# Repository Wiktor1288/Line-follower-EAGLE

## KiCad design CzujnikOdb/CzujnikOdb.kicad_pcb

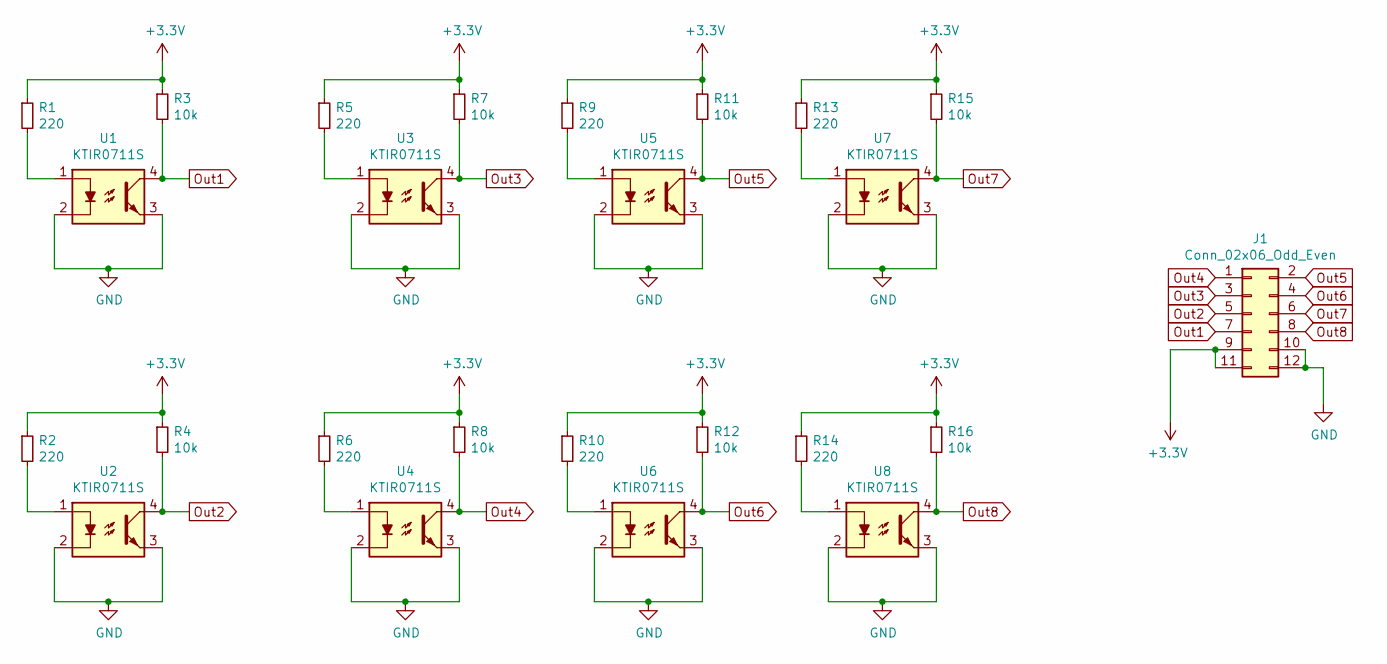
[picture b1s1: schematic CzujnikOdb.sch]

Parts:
J1: Conn_02x06_Odd_Even; PinHeader_2x06_P2.54mm_Vertical
R1, R2, R5, R6, R9, R10, R13, R14: 220; R_0805_2012Metric_Pad1.20x1.40mm_HandSolder
R3, R4, R7, R8, R11, R12, R15, R16: 10k; R_0805_2012Metric_Pad1.20x1.40mm_HandSolder
U1, U2, U3, U4, U5, U6, U7, U8: KTIR0711S

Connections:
+3V3: J1.9, J1.11, R1.1, R2.1, R3.1, R4.1, R5.1, R6.1, R7.1, R8.1, R9.1, R10.1, R11.1, R12.1, R13.1, R14.1, R15.1, R16.1
GND: J1.10, J1.12, U1.2, U1.3, U2.2, U2.3, U3.2, U3.3, U4.2, U4.3, U5.2, U5.3, U6.2, U6.3, U7.2, U7.3, U8.2, U8.3
unnamed: R1.2, U1.1
unnamed: R2.2, U2.1
unnamed: R5.2, U3.1
unnamed: R6.2, U4.1
unnamed: R9.2, U5.1
unnamed: R10.2, U6.1
unnamed: R13.2, U7.1
unnamed: R14.2, U8.1
Out1: J1.7, R3.2, U1.4
Out2: J1.5, R4.2, U2.4
Out3: J1.3, R7.2, U3.4
Out4: J1.1, R8.2, U4.4
Out5: J1.2, R11.2, U5.4
Out6: J1.4, R12.2, U6.4
Out7: J1.6, R15.2, U7.4
Out8: J1.8, R16.2, U8.4

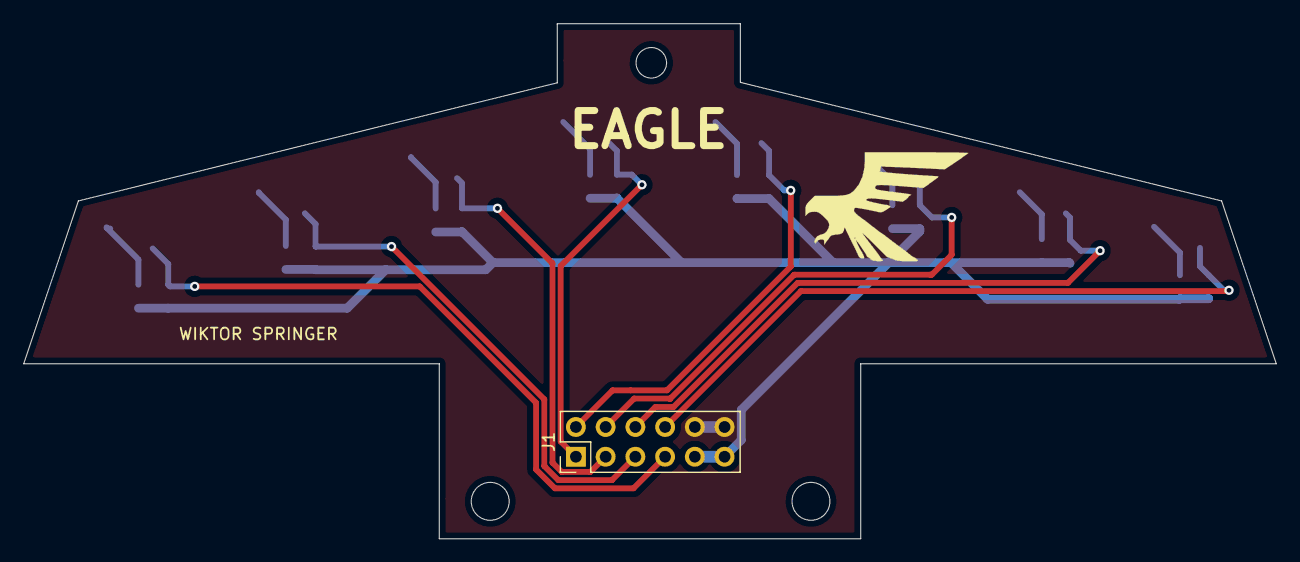
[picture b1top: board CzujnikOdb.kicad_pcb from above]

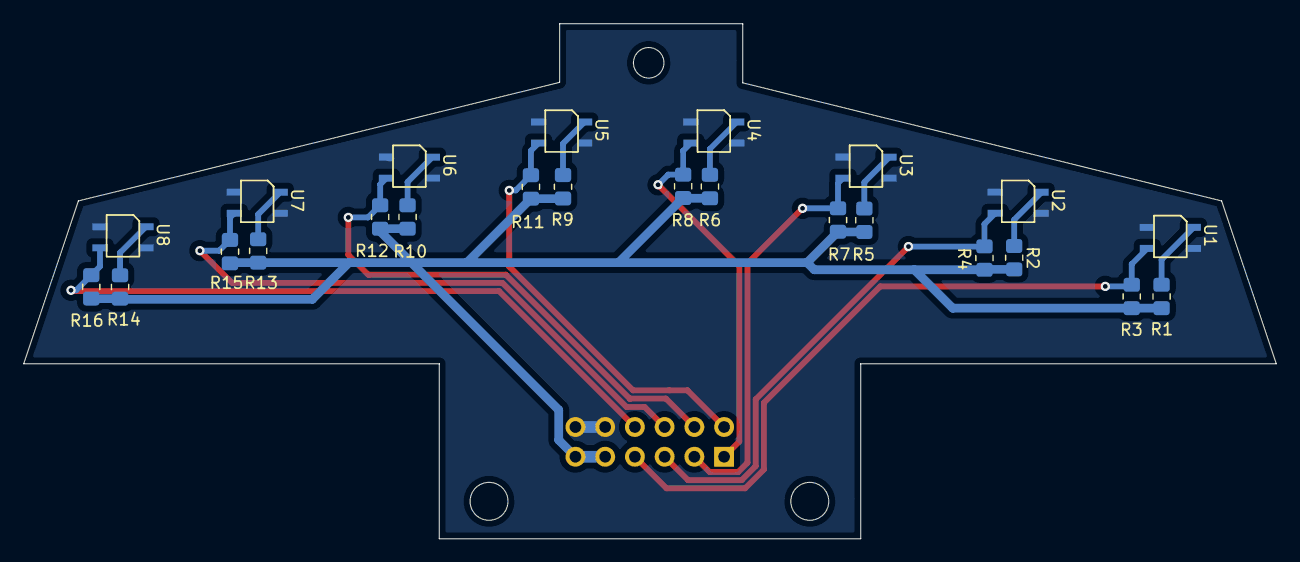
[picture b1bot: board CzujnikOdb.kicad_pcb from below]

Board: 2 copper layers, 107.0 x 44.0 mm, 25 parts (24 on the bottom side), 18 nets.

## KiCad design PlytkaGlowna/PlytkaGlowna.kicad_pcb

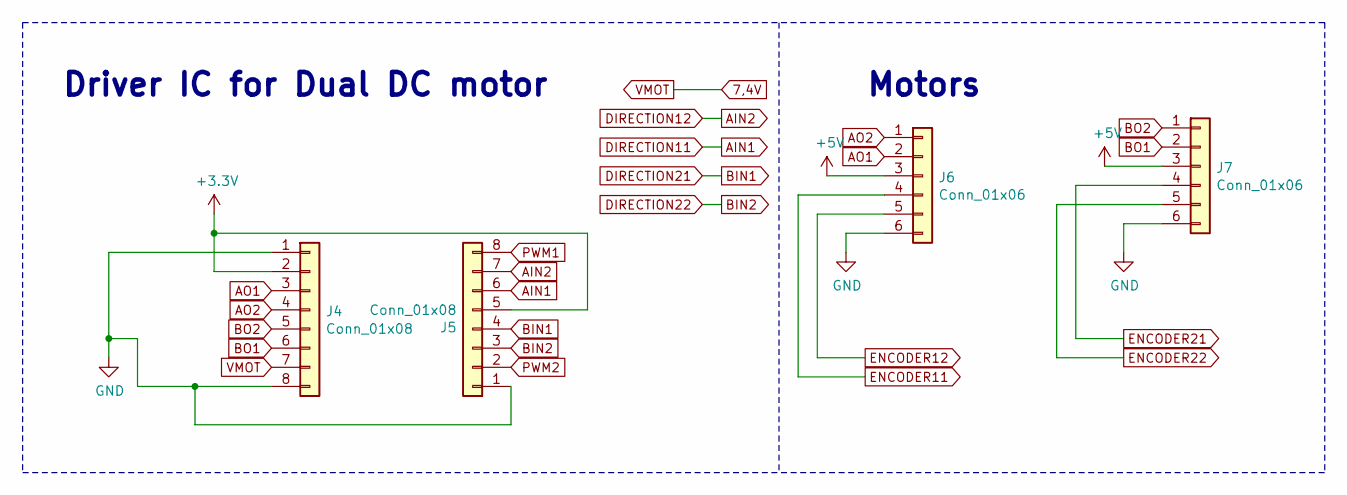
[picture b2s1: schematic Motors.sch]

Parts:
J4, J5: Conn_01x08; PinSocket_1x08_P2.54mm_Vertical
J6, J7: Conn_01x06; PinSocket_1x06_P2.54mm_Vertical

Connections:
7,4V: J4.7; also elsewhere on the board
+5V: J6.3, J7.3; also elsewhere on the board
AIN1: J5.6; also elsewhere on the board
AIN2: J5.7; also elsewhere on the board
AO1: J4.3, J6.2
AO2: J4.4, J6.1
BIN1: J5.4; also elsewhere on the board
BIN2: J5.3; also elsewhere on the board
BO1: J4.6, J7.2
BO2: J4.5, J7.1
ENCODER11: J6.4; also elsewhere on the board
ENCODER12: J6.5; also elsewhere on the board
ENCODER21: J7.4; also elsewhere on the board
ENCODER22: J7.5; also elsewhere on the board
GND: J4.1, J4.8, J5.1, J6.6, J7.6; also elsewhere on the board
PWM1: J5.8; also elsewhere on the board
PWM2: J5.2; also elsewhere on the board
VDD: J4.2, J5.5; also elsewhere on the board

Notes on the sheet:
Driver IC for Dual DC motor
Motors

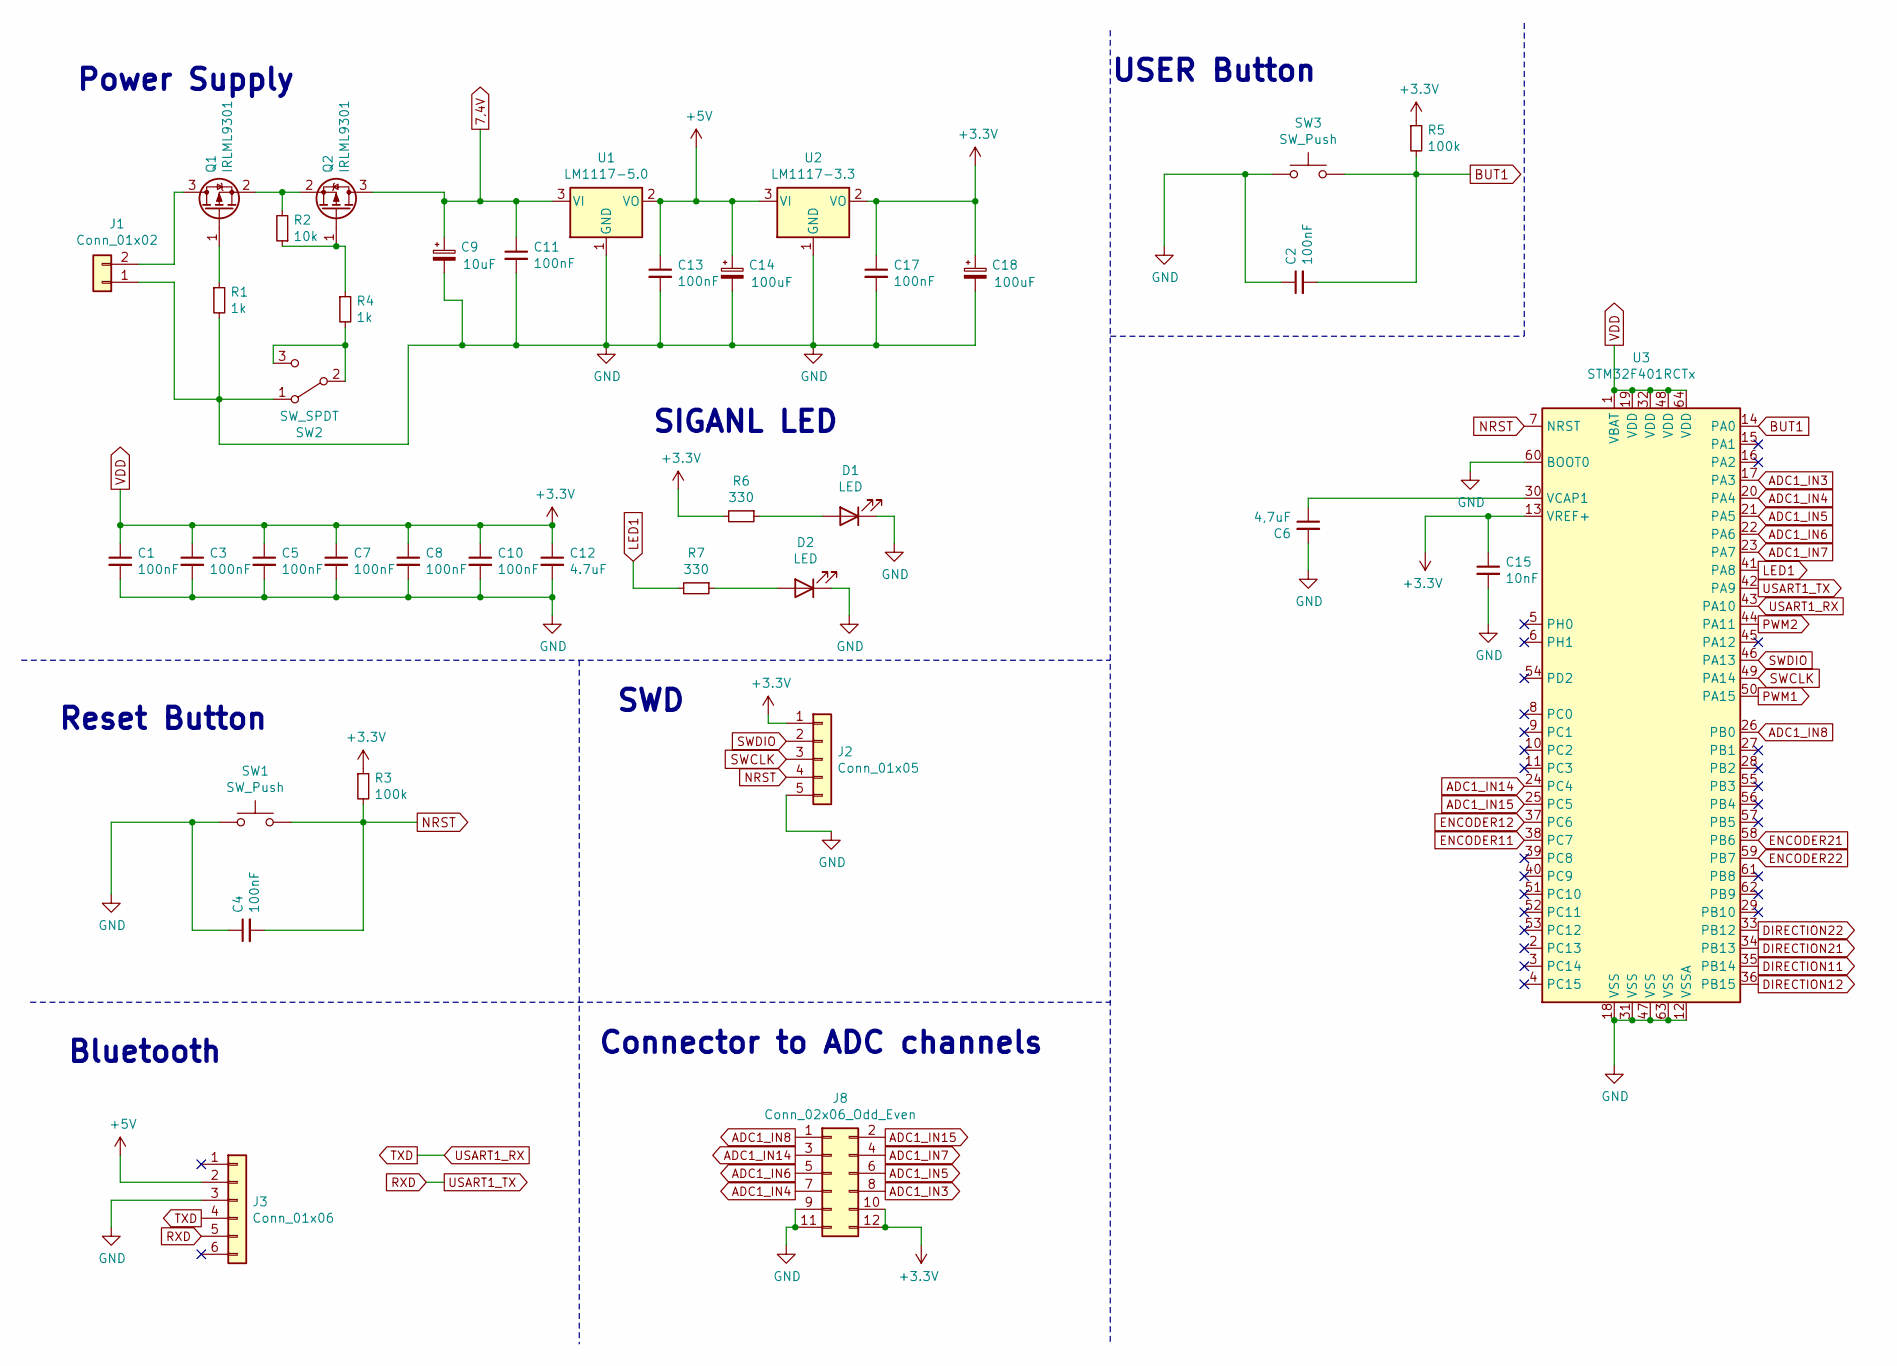
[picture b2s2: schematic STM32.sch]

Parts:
C1, C2, C3, C4, C5, C7, C8, C10, C11, C13: 100nF; C_0805_2012Metric_Pad1.18x1.45mm_HandSolder
C6: 4,7uF; C_0603_1608Metric_Pad1.08x0.95mm_HandSolder
C9: 10uF; CP_Elec_4x5.4
C12: 4.7uF; C_0603_1608Metric_Pad1.08x0.95mm_HandSolder
C14, C18: 100uF; CP_Elec_6.3x5.4
C15: 10nF; C_0805_2012Metric_Pad1.18x1.45mm_HandSolder
C17: 100nF; C_0603_1608Metric_Pad1.08x0.95mm_HandSolder
D1, D2: LED; LED_D5.0mm
J1: Conn_01x02; JST_EH_B2B-EH-A_1x02_P2.50mm_Vertical
J2: Conn_01x05; PinSocket_1x05_P2.54mm_Vertical
J3: Conn_01x06; PinSocket_1x06_P2.54mm_Vertical
J8: Conn_02x06_Odd_Even; PinHeader_2x06_P2.54mm_Vertical
Q1, Q2: IRLML9301; SOT-23
R1, R4: 1k; R_0805_2012Metric_Pad1.20x1.40mm_HandSolder
R2: 10k; R_0805_2012Metric_Pad1.20x1.40mm_HandSolder
R3, R5: 100k; R_0805_2012Metric_Pad1.20x1.40mm_HandSolder
R6, R7: 330; R_0805_2012Metric_Pad1.20x1.40mm_HandSolder
SW1, SW3: SW_Push; TactSwitchSMD
SW2: SW_SPDT; Przelacznik
U1: LM1117-5.0; SOT-223-3_TabPin2
U2: LM1117-3.3; SOT-223-3_TabPin2
U3: STM32F401RCTx; LQFP-64_10x10mm_P0.5mm

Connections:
7,4V: C9.1, C11.1, Q2.3 (D), U1.3 (VI); also elsewhere on the board
+5V: C13.1, C14.1, J3.2, U1.2 (VO), U2.3 (VI); also elsewhere on the board
ADC1_IN3: J8.8, U3.17 (PA3)
ADC1_IN4: J8.7, U3.20 (PA4)
ADC1_IN5: J8.6, U3.21 (PA5)
ADC1_IN6: J8.5, U3.22 (PA6)
ADC1_IN7: J8.4, U3.23 (PA7)
ADC1_IN8: J8.1, U3.26 (PB0)
ADC1_IN14: J8.3, U3.24 (PC4)
ADC1_IN15: J8.2, U3.25 (PC5)
AIN1: U3.35 (PB14); also elsewhere on the board
AIN2: U3.36 (PB15); also elsewhere on the board
BIN1: U3.34 (PB13); also elsewhere on the board
BIN2: U3.33 (PB12); also elsewhere on the board
BUT1: C2.2, R5.2, SW3.2, U3.14 (PA0)
ENCODER11: U3.38 (PC7); also elsewhere on the board
ENCODER12: U3.37 (PC6); also elsewhere on the board
ENCODER21: U3.58 (PB6); also elsewhere on the board
ENCODER22: U3.59 (PB7); also elsewhere on the board
GND: C1.2, C2.1, C3.2, C4.1, C5.2, C6.2, C7.2, C8.2, C9.2, C10.2, C11.2, C12.2, C13.2, C14.2, C15.2, C17.2, C18.2, D1.1 (K), D2.1 (K), J1.1, J2.5, J3.3, J8.9, J8.11, R1.2, SW1.1, SW2.1 (A), SW3.1, U1.1 (GND), U2.1 (GND), U3.12 (VSSA), U3.18 (VSS), U3.31 (VSS), U3.47 (VSS), U3.60 (BOOT0), U3.63 (VSS); also elsewhere on the board
LED1: R7.2, U3.41 (PA8)
NRST: C4.2, J2.4, R3.2, SW1.2, U3.7 (NRST)
unnamed: C6.1, U3.30 (VCAP1)
unnamed: D1.2 (A), R6.1
unnamed: D2.2 (A), R7.1
unnamed: J1.2, Q1.3 (D)
unnamed: Q1.1 (G), R1.1
unnamed: Q1.2 (S), Q2.2 (S), R2.2
unnamed: Q2.1 (G), R2.1, R4.1
unnamed: R4.2, SW2.2 (B), SW2.3 (C)
PWM1: U3.50 (PA15); also elsewhere on the board
PWM2: U3.44 (PA11); also elsewhere on the board
RXD: J3.5, U3.42 (PA9)
SWCLK: J2.3, U3.49 (PA14)
SWDIO: J2.2, U3.46 (PA13)
TXD: J3.4, U3.43 (PA10)
VDD: C1.1, C3.1, C5.1, C7.1, C8.1, C10.1, C12.1, C15.1, C17.1, C18.1, J2.1, J8.10, J8.12, R3.1, R5.1, R6.2, U2.2 (VO), U3.1 (VBAT), U3.13 (VREF+), U3.19 (VDD), U3.32 (VDD), U3.48 (VDD), U3.64 (VDD); also elsewhere on the board

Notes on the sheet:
Power Supply
Reset Button
SWD
Connector to ADC channels
Bluetooth
USER Button
SIGANL LED

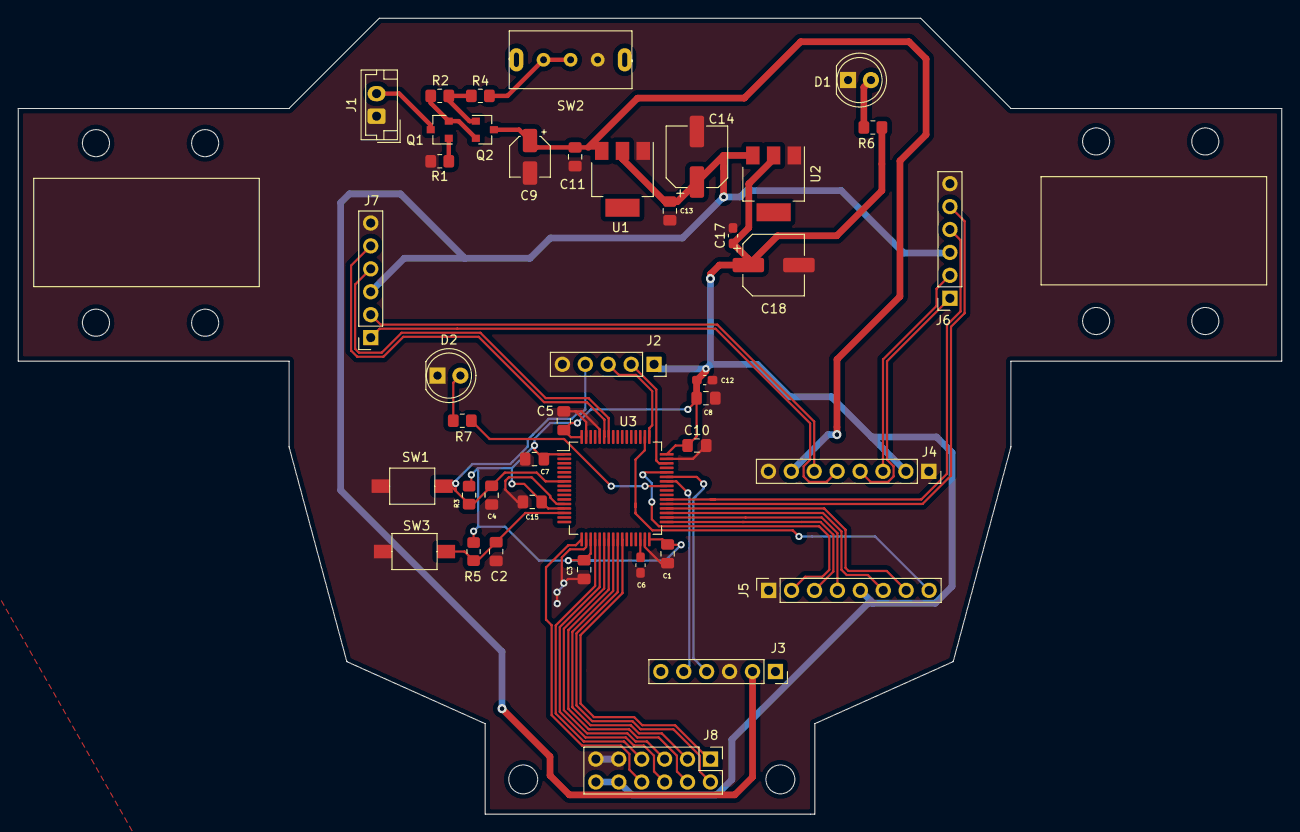
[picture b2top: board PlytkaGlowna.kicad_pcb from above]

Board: 2 copper layers, 140.0 x 88.2 mm, 42 parts (0 on the bottom side), 41 nets.

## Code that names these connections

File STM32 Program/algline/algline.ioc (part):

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Mcu.Name=STM32F401R(B-C)Tx
Mcu.Package=LQFP64
Mcu.UserName=STM32F401RCTx
PA0-WKUP.GPIOParameters=GPIO_Label,GPIO_ModeDefaultEXTI
PA0-WKUP.GPIO_Label=BUT1
PA0-WKUP.GPIO_ModeDefaultEXTI=GPIO_MODE_IT_FALLING
PA0-WKUP.Signal=GPXTI0
PA10.Mode=Asynchronous
PA10.Signal=USART1_RX
PA11.Signal=S_TIM1_CH4
PA13.Mode=Serial_Wire
PA13.Signal=SYS_JTMS-SWDIO
PA14.Mode=Serial_Wire
PA14.Signal=SYS_JTCK-SWCLK
PA15.Signal=S_TIM2_CH1_ETR
PA3.Signal=ADCx_IN3
PA4.Signal=ADCx_IN4
PA5.Signal=ADCx_IN5
PA6.Signal=ADCx_IN6
PA7.Signal=ADCx_IN7
PA8.GPIOParameters=GPIO_Label
PA8.GPIO_Label=LED1
PA8.Signal=GPIO_Output
PA9.Mode=Asynchronous
PA9.Signal=USART1_TX
PB0.Signal=ADCx_IN8
PB12.GPIOParameters=GPIO_Label
PB12.GPIO_Label=D22
PB12.Signal=GPIO_Output
PB13.GPIOParameters=GPIO_Label
PB13.GPIO_Label=D21
PB13.Signal=GPIO_Output
PB14.GPIOParameters=GPIO_Label
PB14.GPIO_Label=D11
PB14.Signal=GPIO_Output
PB15.GPIOParameters=GPIO_Label
PB15.GPIO_Label=D12
PB15.Signal=GPIO_Output
PC4.Signal=ADCx_IN14
PC5.Signal=ADCx_IN15
RCC.HSE_VALUE=25000000
RCC.SYSCLKFreq_VALUE=84000000
RCC.SYSCLKSource=RCC_SYSCLKSOURCE_PLLCLK
board=custom

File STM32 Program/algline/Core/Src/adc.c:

/**
  ******************************************************************************
  * File Name          : ADC.c
  * Description        : This file provides code for the configuration
  *                      of the ADC instances.
  ******************************************************************************
  * @attention
  *
  * <h2><center>&copy; Copyright (c) 2021 STMicroelectronics.
  * All rights reserved.</center></h2>
  *
  * This software component is licensed by ST under BSD 3-Clause license,
  * the "License"; You may not use this file except in compliance with the
  * License. You may obtain a copy of the License at:
  *                        opensource.org/licenses/BSD-3-Clause
  *
  ******************************************************************************
  */

/* Includes ------------------------------------------------------------------*/
#include "adc.h"

/* USER CODE BEGIN 0 */

/* USER CODE END 0 */

ADC_HandleTypeDef hadc1;
DMA_HandleTypeDef hdma_adc1;

/* ADC1 init function */
void MX_ADC1_Init(void)
{
  ADC_ChannelConfTypeDef sConfig = {0};

  /** Configure the global features of the ADC (Clock, Resolution, Data Alignment and number of conversion)
  */
  hadc1.Instance = ADC1;
  hadc1.Init.ClockPrescaler = ADC_CLOCK_SYNC_PCLK_DIV4;
  hadc1.Init.Resolution = ADC_RESOLUTION_12B;
  hadc1.Init.ScanConvMode = ENABLE;
  hadc1.Init.ContinuousConvMode = ENABLE;
  hadc1.Init.DiscontinuousConvMode = DISABLE;
  hadc1.Init.ExternalTrigConvEdge = ADC_EXTERNALTRIGCONVEDGE_NONE;
  hadc1.Init.ExternalTrigConv = ADC_SOFTWARE_START;
  hadc1.Init.DataAlign = ADC_DATAALIGN_RIGHT;
  hadc1.Init.NbrOfConversion = 8;
  hadc1.Init.DMAContinuousRequests = ENABLE;
  hadc1.Init.EOCSelection = ADC_EOC_SINGLE_CONV;
  if (HAL_ADC_Init(&hadc1) != HAL_OK)
  {
    Error_Handler();
  }
  /** Configure for the selected ADC regular channel its corresponding rank in the sequencer and its sample time.
  */
  sConfig.Channel = ADC_CHANNEL_3;
  sConfig.Rank = 1;
  sConfig.SamplingTime = ADC_SAMPLETIME_56CYCLES;
  if (HAL_ADC_ConfigChannel(&hadc1, &sConfig) != HAL_OK)
  {
    Error_Handler();
  }
  /** Configure for the selected ADC regular channel its corresponding rank in the sequencer and its sample time.
  */
  sConfig.Channel = ADC_CHANNEL_4;
  sConfig.Rank = 2;
  if (HAL_ADC_ConfigChannel(&hadc1, &sConfig) != HAL_OK)
  {
    Error_Handler();
  }
  /** Configure for the selected ADC regular channel its corresponding rank in the sequencer and its sample time.
  */
  sConfig.Channel = ADC_CHANNEL_5;
  sConfig.Rank = 3;
  if (HAL_ADC_ConfigChannel(&hadc1, &sConfig) != HAL_OK)
  {
    Error_Handler();
  }
  /** Configure for the selected ADC regular channel its corresponding rank in the sequencer and its sample time.
  */
  sConfig.Channel = ADC_CHANNEL_6;
  sConfig.Rank = 4;
  if (HAL_ADC_ConfigChannel(&hadc1, &sConfig) != HAL_OK)
  {
    Error_Handler();
  }
  /** Configure for the selected ADC regular channel its corresponding rank in the sequencer and its sample time.
  */
  sConfig.Channel = ADC_CHANNEL_7;
  sConfig.Rank = 5;
  if (HAL_ADC_ConfigChannel(&hadc1, &sConfig) != HAL_OK)
  {
    Error_Handler();
  }
  /** Configure for the selected ADC regular channel its corresponding rank in the sequencer and its sample time.
  */
  sConfig.Channel = ADC_CHANNEL_8;
  sConfig.Rank = 6;
  if (HAL_ADC_ConfigChannel(&hadc1, &sConfig) != HAL_OK)
  {
    Error_Handler();
  }
  /** Configure for the selected ADC regular channel its corresponding rank in the sequencer and its sample time.
  */
  sConfig.Channel = ADC_CHANNEL_14;
  sConfig.Rank = 7;
  if (HAL_ADC_ConfigChannel(&hadc1, &sConfig) != HAL_OK)
  {
    Error_Handler();
  }
  /** Configure for the selected ADC regular channel its corresponding rank in the sequencer and its sample time.
  */
  sConfig.Channel = ADC_CHANNEL_15;
  sConfig.Rank = 8;
  if (HAL_ADC_ConfigChannel(&hadc1, &sConfig) != HAL_OK)
  {
    Error_Handler();
  }

}

void HAL_ADC_MspInit(ADC_HandleTypeDef* adcHandle)
{

  GPIO_InitTypeDef GPIO_InitStruct = {0};
  if(adcHandle->Instance==ADC1)
  {
  /* USER CODE BEGIN ADC1_MspInit 0 */

  /* USER CODE END ADC1_MspInit 0 */
    /* ADC1 clock enable */
    __HAL_RCC_ADC1_CLK_ENABLE();

    __HAL_RCC_GPIOA_CLK_ENABLE();
    __HAL_RCC_GPIOC_CLK_ENABLE();
    __HAL_RCC_GPIOB_CLK_ENABLE();
    /**ADC1 GPIO Configuration
    PA3     ------> ADC1_IN3
    PA4     ------> ADC1_IN4
    PA5     ------> ADC1_IN5
    PA6     ------> ADC1_IN6
    PA7     ------> ADC1_IN7
    PC4     ------> ADC1_IN14
    PC5     ------> ADC1_IN15
    PB0     ------> ADC1_IN8
    */
    GPIO_InitStruct.Pin = GPIO_PIN_3|GPIO_PIN_4|GPIO_PIN_5|GPIO_PIN_6
                          |GPIO_PIN_7;
    GPIO_InitStruct.Mode = GPIO_MODE_ANALOG;
    GPIO_InitStruct.Pull = GPIO_NOPULL;
    HAL_GPIO_Init(GPIOA, &GPIO_InitStruct);

    GPIO_InitStruct.Pin = GPIO_PIN_4|GPIO_PIN_5;
    GPIO_InitStruct.Mode = GPIO_MODE_ANALOG;
    GPIO_InitStruct.Pull = GPIO_NOPULL;
    HAL_GPIO_Init(GPIOC, &GPIO_InitStruct);

    GPIO_InitStruct.Pin = GPIO_PIN_0;
    GPIO_InitStruct.Mode = GPIO_MODE_ANALOG;
    GPIO_InitStruct.Pull = GPIO_NOPULL;
    HAL_GPIO_Init(GPIOB, &GPIO_InitStruct);

    /* ADC1 DMA Init */
    /* ADC1 Init */
    hdma_adc1.Instance = DMA2_Stream0;
    hdma_adc1.Init.Channel = DMA_CHANNEL_0;
    hdma_adc1.Init.Direction = DMA_PERIPH_TO_MEMORY;
    hdma_adc1.Init.PeriphInc = DMA_PINC_DISABLE;
    hdma_adc1.Init.MemInc = DMA_MINC_ENABLE;
    hdma_adc1.Init.PeriphDataAlignment = DMA_PDATAALIGN_HALFWORD;
    hdma_adc1.Init.MemDataAlignment = DMA_MDATAALIGN_HALFWORD;
    hdma_adc1.Init.Mode = DMA_CIRCULAR;
    hdma_adc1.Init.Priority = DMA_PRIORITY_LOW;
    hdma_adc1.Init.FIFOMode = DMA_FIFOMODE_DISABLE;
    if (HAL_DMA_Init(&hdma_adc1) != HAL_OK)
    {
      Error_Handler();
    }

    __HAL_LINKDMA(adcHandle,DMA_Handle,hdma_adc1);

  /* USER CODE BEGIN ADC1_MspInit 1 */

  /* USER CODE END ADC1_MspInit 1 */
  }
}

void HAL_ADC_MspDeInit(ADC_HandleTypeDef* adcHandle)
{

  if(adcHandle->Instance==ADC1)
  {
  /* USER CODE BEGIN ADC1_MspDeInit 0 */

  /* USER CODE END ADC1_MspDeInit 0 */
    /* Peripheral clock disable */
    __HAL_RCC_ADC1_CLK_DISABLE();

    /**ADC1 GPIO Configuration
    PA3     ------> ADC1_IN3
    PA4     ------> ADC1_IN4
    PA5     ------> ADC1_IN5
    PA6     ------> ADC1_IN6
    PA7     ------> ADC1_IN7
    PC4     ------> ADC1_IN14
    PC5     ------> ADC1_IN15
    PB0     ------> ADC1_IN8
    */
    HAL_GPIO_DeInit(GPIOA, GPIO_PIN_3|GPIO_PIN_4|GPIO_PIN_5|GPIO_PIN_6
                          |GPIO_PIN_7);

    HAL_GPIO_DeInit(GPIOC, GPIO_PIN_4|GPIO_PIN_5);

    HAL_GPIO_DeInit(GPIOB, GPIO_PIN_0);

    /* ADC1 DMA DeInit */
    HAL_DMA_DeInit(adcHandle->DMA_Handle);
  /* USER CODE BEGIN ADC1_MspDeInit 1 */

  /* USER CODE END ADC1_MspDeInit 1 */
  }
}

/* USER CODE BEGIN 1 */

/* USER CODE END 1 */

/************************ (C) COPYRIGHT STMicroelectronics *****END OF FILE****/

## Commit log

2021-05-02 Dodanie schematu i projekt PCB przod
2021-05-05 plytka glowna
    Dodanie projektu PCB plytki glownej
2021-05-10 next version of PCBs
    Next version of PCBs
2021-05-11 final version 1
    i hope
2021-05-13 Final version v2
2021-06-08 end of work
